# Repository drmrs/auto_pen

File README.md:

# Auto Penetrator

The project consists of a top to bottom open source 3d printed automatic penetrator.

If you can install and ssh into a linux box and have a 3d printed you should be able to make this.

# Gallery

[Youtube Video](https://www.youtube.com/watch?v=6sc3pjCMek8)

# Assembly & Use

Start with `hardware/README.md` file and follow the instructions from there.

# Open Source

The hardware is licenced under the CERN OHL (Basally GPL for hardware in so much as that can be enforced.)
The software is licenced under the Affero GPL.

# How To Help

Improvements are always welcome and PRs generally will be accepted.

Specific ways people can help include:
- Finding and fixing typos.
- Creating profiles for other raspberry pis beyond the original.
- Improving the code base.
- Adding more modes
- Improving the hardware diesign
    - Replacing glued on parts with screws
    - Add a screw mount for the USB adapter.
    - Adding a screw mount for the raspberry pi.

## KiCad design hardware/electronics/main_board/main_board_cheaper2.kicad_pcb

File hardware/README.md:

# Open Source Automatic Penetrator

## Building

Note in these images you may see some badly printed parts. You should aim to do better. These parts where the results of me wanting to finish and publish this documentation.

### Tools
1. Metric allen wrench set
2. 3D printer (300mmx300mm) is ideal but a smaller one works too.

### Materials

I will provide links to where I bought mine but you do not have to buy the same item or from the same source. My goals where to do this as economically as possible. Your goals may be different or the purchasing environment may have changed.  

The total cost of this build assuming you own all of the tools is: $201.98. This leaves you with many bolts, screws and parts that you can use for future projects.

If you already have some of these parts the price will be even lower.

#### Nuts & Bolts
1. x4 20mm (or longer) countersunk m3 screws [AliExpress $2.55](https://www.aliexpress.com/item/33007545714.html)
2. x16 m3 nuts [AliExpress $1.89](https://www.aliexpress.com/item/33031240097.html)
3. x4 10mm countersunk m3 screws [AliExpress $1.64](https://www.aliexpress.com/item/33007545714.html)
4. x2 12mm m3 screws [AliExpress $1.74](https://www.aliexpress.com/item/33007545714.html)

#### Electronics
1. NEMA34 Stepper Motor [Stepper Motor / Controller Kit AliExpress $84.19](https://www.aliexpress.com/item/33025486138.html)
2. Stepper Motor Controller [Part of Kit $0](#)
3. 24v 5A DC Power Supply [AliExpress $11.34](https://www.aliexpress.com/item/32905696401.html)
4. 24v USB charger [AliExpress $3.00](https://www.aliexpress.com/item/33031240097.html)
5. MicroUSB/USB C Cable (matching your raspberry pi) [Spare $0](#)
6. Raspberry Pi [Spare $40](https://www.raspberrypi.org/products/)
7. Barrel Jacks [Amazon $9.89](https://www.amazon.com/43x2pcs-Connectors-Security-Lighting-MILAPEAK)
8 18AWG Wire [AliExpress $4.88](https://www.aliexpress.com/item/32903241720.html)

#### Misc.
1. A roll of pla filament [Amazon $16](https://www.amazon.com/s?k=pla+1.75mm+filament)
2. Super Glue [Amazon $3.97](https://www.amazon.com/Loctite-Ultra-Control-4-Gram-1363589)
3. 14" Drawer Slide [Amazon $13.99](https://www.amazon.com/AmazonBasics-Bearing-Drawer-Slides-Plated-Steel/dp/B01MZC15UG)
4. Female Breadboard Jumper Wires [Amazon $6.90](https://www.amazon.com/gp/product/B01EV70C78)

### Step 1: Print Parts

#### 1.1. Main body

All items here printed at 0.3mm layer heights with 10% gyroid infill.

Load the `auto_pen/hardware/bin/main_body.amf` file into your slicer. Break it into its sub-components and lay them out as shown in the image below. If you need to print the items in separate prints this will be fine. If you need to split the items this is also fine. [I recommend you split the main case like this.](TODO)

If you want a pattern / ventilation (highly recommended) on the main case add a modifier block to the lid section (shown in green here) and set the infill to hex or some other cool pattern and set the top and bottom perimeters to 0. It should look like the below.

The two thin objects on thr right hand side of the image need extra strength and should be printed with 6 perimeters and 6 top and bottom layers.

#### 1.2 Rack & Pinion

All items here printed at 0.2mm layer heights with 10% gyroid infill with 4 perimeters and 5 top and bottom layers.

Load and print the rack and pinion from this file `auto_pen/hardware/bin/rack_and_pinion.amf`

It should look like this.

#### 1.3 Stepper Screw Adapters.

All items here printed at 0.2mm layer heights with 10% gyroid infill.

Load and print 4 copies of the screw adapter `auto_pen/hardware/bin/stepper_screw_adapters.amf`

The nut should be facing down and "from build plate only" supports should be enabled.

It should look like this.

Remove the supports and continue.

#### 1.4 Pusher Plate

There are two types of pusher plates, one uses rope to attach your "tool" to the plate, the other is designed for suction-cup tools. Choose the one you prefer.

All items here printed at 0.3mm layer heights with 15% gyroid infill and 8 perimeters.

Load and print the pusher plate you prefer `auto_pen/hardware/bin/rope_pusher_plate.amf` or `auto_pen/hardware/bin/suction_pusher_plate.amf`

The plate should be facing down.

It should look like this.

#### 1.5 Hinges

All items here printed at 0.2mm layer heights with 15% gyroid infill.

Load and print 2 copies of the hinge `auto_pen/hardware/bin/hinge.amf`

It should look like this.

You are Done Printing!

### Step 2: Electronics Assembly

Depending on exactly what you have your wiring may be dine is a slightly different way. If you purchased the exact same items as I did things should be very similar.

A few notes:
1. AC mains power is very dangerous. BE CAREFUL.
2. The Barrel Jack connected to 1 and 2 is connected to mains power. You need to decide the safest way to do this I used a GFIO plug but you may have a safer better way.
3. The Raspberry Pi is plugged into the stepper motor via female breadboard jumper wires with one side stripped off.
4. Different model Raspbery Pis have different GPIO / Ground pin layouts. [Refer to the appropriate documentation](https://www.raspberrypi.org/documentation/usage/gpio/) Make sure the GPIO PIN numbers match what is in the diagram.
5. The USB cable from the Pi should be plugged into the USB 24v adapter.
6. Non Raspberry Pi GPIO wiring is gone with the 18AWG wires.
7. I had to use a hammer to smash the clamps of the 24v USB adapter closed on the 18AWG wire.
8. Make sure your 24v 5A DC Power Supply is set to the correct mains voltage for your region (120v vs 240v)
9. For the default profile you will want to switch your motor controller to 1600steps/revolution. For me this was switch 6 only. Consult your stepper motor's documentation.

[For Full Size click here](https://raw.githubusercontent.com/drmrs/auto_pen/master/hardware/images/wires.png)

### Step 3: Electronics Testing

Assuming all your connections are sound connect mains power to the 24v 5A DC Power Supply. You may hear some sounds and some LEDs may turn on. If you can not turn the spindle of the stepper motor this is good news!

Precede to the `auto_pen/software/README.md` file to set up your Raspberry Pi.Once you can control your stepper motor precede to the next step.

### Step 4: Final Assembly

#### 4.1 Stepper motor

Press m3 nuts into the stepper motor adapter and press the who adapter into the stepper motor such that the the face is flush.

Note: Your nut should press substantially further in then in these images.

Place the case such that stepper motor face is out and the holes on the second face are down.

Slide the stepper motor into the case with the wire facing up.

Using 4 20mm or longer countersunk screws secure the stepper motor in place. These should be tight.

#### 4.2 Power Supply

The Mains -> 24vDC Power supply goes in the back with the connectors facing the stepper and the screw holes facing down.

Push 10mm countersunk screws through the bottom and line them up with with the screw holes.

With one finger press a nut down onto the screw and use an allen wrench to tighten from the outside.

Now is a good time to run the USB cable. RUn it from the USB adapter to the right hand side of the box above the power supply.

#### 4.3 Stepper Motor Controller

Mount the controller in the same way you mounted the power supply positioning the raspberry pi to the right and the USB power adapter above the stepper motor to the left.

The pi might be a tight angle but it should fit. I recommend positioning the PI so the SD card is readily available.

When you are done it should look like this:

Keep the mains power supply above the stepper motor for now.

You may want to retest things before you continue.

#### 4.4 Drawer Slide and Pusher.

Attach the slide to the "feet" via 2 10mm m3 screws. Tighten and ensure they are perpendicular to the slide.

Apply a generous amount of super glue to the top of the feet and place the main case on it such that:

1. The side of the rail is flush against the case.
2. The back of the rail is flush with the back of the case (raspberry pi side)
3. The extending bar is near the stepper motor.

Let dry for 1 hour.

Using 2 12mm m3 screws and nuts lock the rope based pusher into place.

#### 4.5 Rack & Pinion

 Press the gear onto the stepper motor.
 
 With the slider in the locked position position the rack that the gear is not engaged with it. This should be by a few mm. See the photo below. We give it this extra space so in case something goes wrong the rack isn't slammed into the lock.
 
 Glue it in position.

 #### Cover, Hinges and Power
 
 After printing the hinges may be VERY stiff. move them til they loosen up.
 
 With the hinges in the 90 degree position glue them flush against the upper two corners. THe side with the hole is the top. The hole should be on the left-ish side. (See photo below.)
 
 Allow to dry for 30 min.
 
 With the hinges in the 90 angle glue them against the case such that the lid is flush against the case. Be sure not to glue the hinge to the top of the lid.
 
  Allow to dry for 30 min.

 The mains power inlet should friction fit into the hole. Glue it in.

 Close and you are done!

 If the lid is a bit loose you could use some tape or a small drop of super glue to hold it in place.
 
 Enjoy.

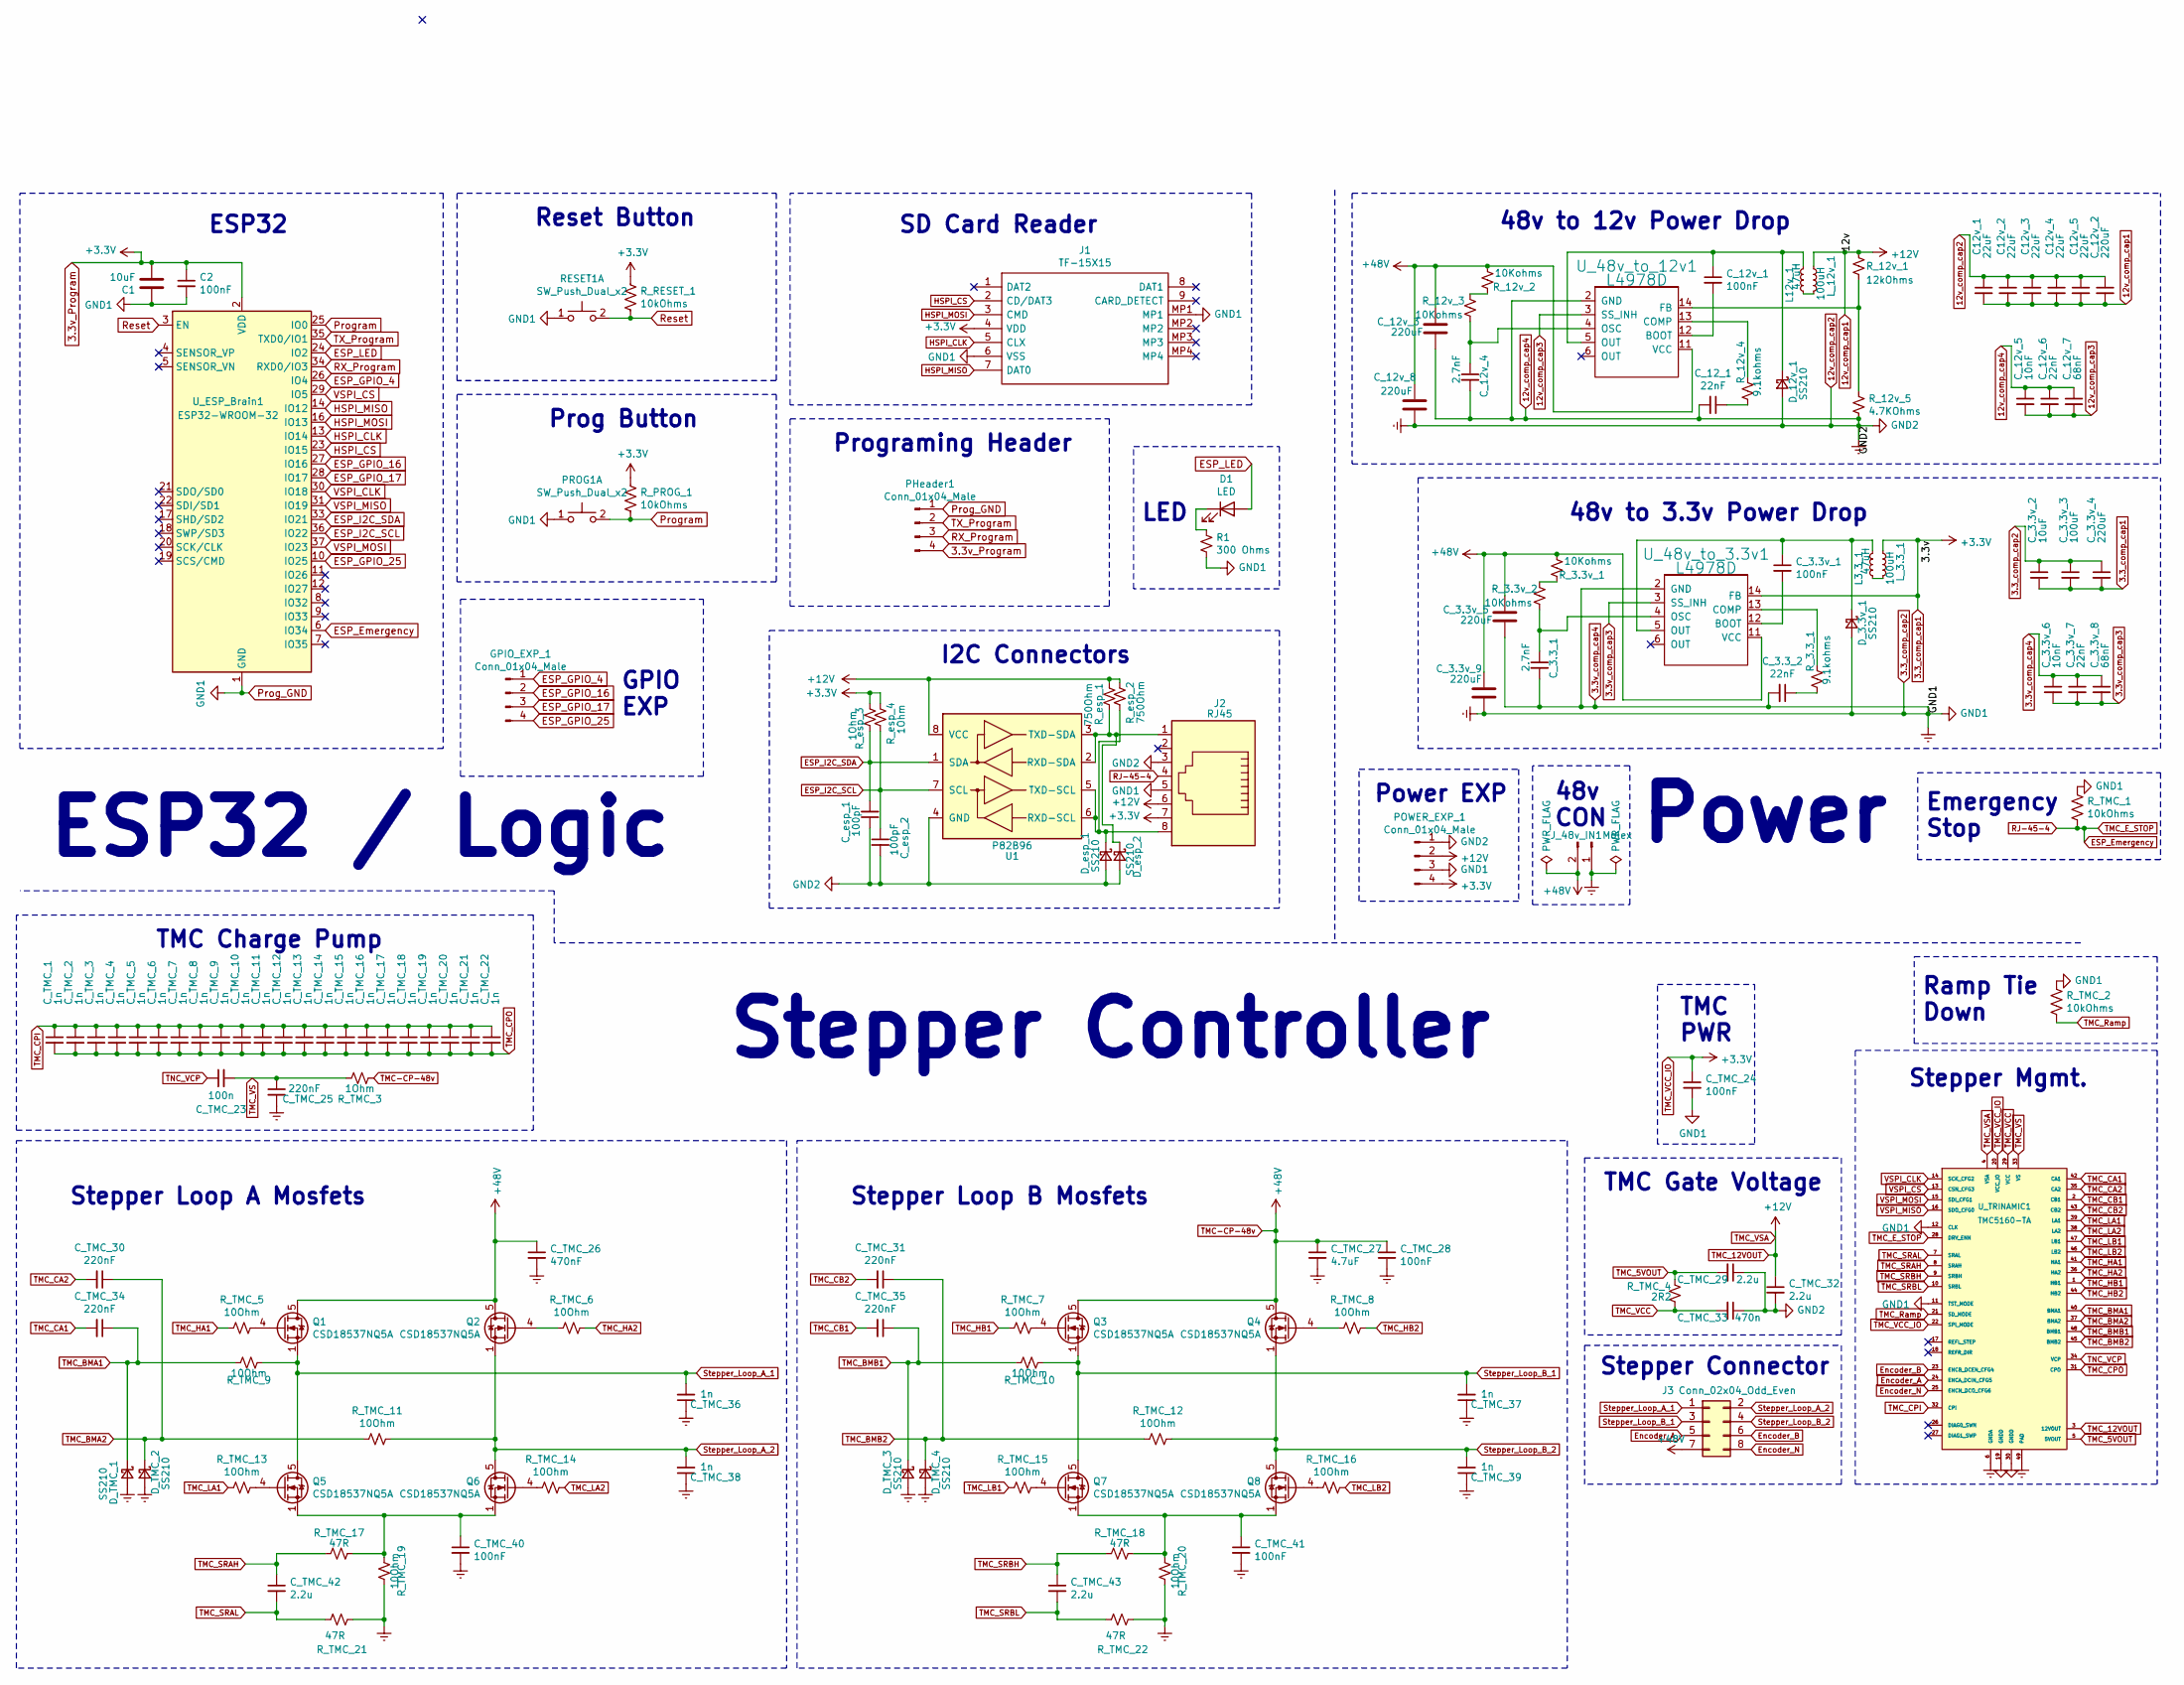
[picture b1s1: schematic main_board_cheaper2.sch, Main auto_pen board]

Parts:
C1: 10uF; C_0402_1005Metric; JLCPCB C15525
C2: 100nF; C_0402_1005Metric; JLCPCB C1525
C12v_1, C12v_2, C12v_3, C12v_4, C12v_5: 22uF; C_0805_2012Metric; JLCPCB C45783
C_3.3_1, C_12v_4: 2.7nF; C_0603_1608Metric; JLCPCB C1609
C_3.3_2, C_3.3v_7, C_12_1, C_12v_6: 22nF; C_0805_2012Metric; JLCPCB C1729
C_3.3v_1, C_12v_1: 100nF; C_0402_1005Metric; JLCPCB C1525
C_3.3v_2: 10uF; C_0402_1005Metric; JLCPCB C15525
C_3.3v_3: 100uF; CP_EIA-3528-15_AVX-H; JLCPCB C16133
C_3.3v_4, C_3.3v_5, C_3.3v_9, C_12v_2, C_12v_3, C_12v_8: 220uF; C_Elec_10x10.2; JLCPCB C3358
C_3.3v_6, C_12v_5: 10nF; C_0805_2012Metric; JLCPCB C1710
C_3.3v_8, C_12v_7: 68nF; C_0603_1608Metric; JLCPCB C31658
C_TMC_1, C_TMC_2, C_TMC_3, C_TMC_4, C_TMC_5, C_TMC_6, C_TMC_7, C_TMC_8, C_TMC_9, C_TMC_10, C_TMC_11, C_TMC_12, C_TMC_13, C_TMC_14, C_TMC_15, C_TMC_16, C_TMC_17, C_TMC_18, C_TMC_19, C_TMC_20, C_TMC_21, C_TMC_22, C_TMC_36, C_TMC_37, C_TMC_38, C_TMC_39: 1n; C_1206_3216Metric; JLCPCB C35216
C_TMC_23: 100n; C_0402_1005Metric; JLCPCB C1525
C_TMC_24: 100nF; C_0402_1005Metric; JLCPCB C1525
C_TMC_25: 220nF; C_0805_2012Metric; JLCPCB C5378
C_TMC_26: 470nF; C_0805_2012Metric; JLCPCB C13967
C_TMC_27: 4.7uF; C_1206_3216Metric; JLCPCB C29823
C_TMC_28, C_TMC_40, C_TMC_41: 100nF; C_1206_3216Metric; JLCPCB C24497
C_TMC_29, C_TMC_32: 2.2u; C_0603_1608Metric; JLCPCB C23630
C_TMC_30, C_TMC_31, C_TMC_34, C_TMC_35: 220nF; C_1206_3216Metric; JLCPCB C1857
C_TMC_33: 470n; C_0603_1608Metric; JLCPCB C1623
C_TMC_42, C_TMC_43: 2.2u; C_1206_3216Metric; JLCPCB C50254
C_esp_1, C_esp_2: 100pF; C_0603_1608Metric; JLCPCB C14858
D1: LED; LED_0603_1608Metric; JLCPCB C72041
D_3.3v_1, D_12v_1: SS210; D_SMA; JLCPCB C14996
D_TMC_1, D_TMC_2, D_TMC_3, D_TMC_4: SS210; D_SMA; JLCPCB C14996
D_esp_1, D_esp_2: SS210; D_SMA; JLCPCB C14996
GPIO_EXP_1: Conn_01x04_Male; PinHeader_1x04_P2.54mm_Vertical; JLCPCB C124378
J1: TF-15X15; TF15X15; Manufacturer_Part_Number TF-15X15; JLCPCB C111196
J2: RJ45; 5555166-1; JLCPCB C305991
J3: Conn_02x04_Odd_Even; Molex_Micro-Fit_3.0_43045-0812_2x04_P3.00mm_Vertical; JLCPCB C277661
J_48v_IN1: Molex; Molex_Micro-Fit_3.0_43045-0212_2x01_P3.00mm_Vertical; JLCPCB C293362
L3.3_1, L12v_1: 47uH; L_0805_2012Metric; JLCPCB C14304
L_3.3_1, L_12v_1: 100uH; L_0805_2012Metric; JLCPCB C68035
PHeader1: Conn_01x04_Male; PinHeader_1x04_P2.54mm_Vertical; JLCPCB C124378
POWER_EXP_1: Conn_01x04_Male; PinHeader_1x04_P2.54mm_Vertical; JLCPCB C124378
PROG1: SW_Push_Dual_x2; SW_Push_1P1T_NO_6x6mm_H9.5mm; JLCPCB C381038
Q1, Q2, Q3, Q4, Q5, Q6, Q7, Q8: CSD18537NQ5A; TDSON-8-1; JLCPCB C72266
R1: 300 Ohms; R_0805_2012Metric; JLCPCB C17617
RESET1: SW_Push_Dual_x2; SW_Push_1P1T_NO_6x6mm_H9.5mm; JLCPCB C381038
R_3.3_1, R_12v_4: 9.1kohms; R_0805_2012Metric; JLCPCB C17855
R_3.3v_1, R_3.3v_2, R_12v_2, R_12v_3: 10Kohms; R_1206_3216Metric; JLCPCB C17902
R_12v_1: 12kOhms; R_0805_2012Metric; JLCPCB C17444
R_12v_5: 4.7KOhms; R_1206_3216Metric; JLCPCB C17936
R_PROG_1: 10kOhms; R_1206_3216Metric; JLCPCB C17902
R_RESET_1: 10kOhms; R_1206_3216Metric; JLCPCB C17902
R_TMC_1, R_TMC_2: 10kOhms; R_1206_3216Metric; JLCPCB C17902
R_TMC_3: 1Ohm; R_1206_3216Metric; JLCPCB C17928
R_TMC_4: 2R2; R_0805_2012Metric; JLCPCB C17521
R_TMC_5, R_TMC_6, R_TMC_7, R_TMC_8, R_TMC_9, R_TMC_10, R_TMC_11, R_TMC_12, R_TMC_13, R_TMC_14, R_TMC_15, R_TMC_16, R_TMC_19, R_TMC_20: 10Ohm; R_1206_3216Metric; JLCPCB C17903
R_TMC_17, R_TMC_18, R_TMC_21, R_TMC_22: 47R; R_0805_2012Metric; JLCPCB C17714
R_esp_1, R_esp_2: 750Ohm; R_1206_3216Metric; JLCPCB C17985
R_esp_3, R_esp_4: 1Ohm; R_1206_3216Metric; JLCPCB C17928
U1: P82B96; SO-8_3.9x4.9mm_P1.27mm; JLCPCB C32103
U_48v_to_3.3v1, U_48v_to_12v1: L4978D; SOIC-16W_7.5x10.3mm_P1.27mm; JLCPCB C93521
U_ESP_Brain1: ESP32-WROOM-32; JLCPCB C82899
U_TRINAMIC1: TMC5160-TA; eTQFP48; MPN TMC5160-TA; Digi-Key_PN 1460-1249-ND

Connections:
3.3_comp_cap1: C1.2, C2.1, C_3.3v_2.2, C_3.3v_3.2, C_3.3v_4.2, C_TMC_24.1, J1.4 (VDD), J2.7, L_3.3_1.1, PHeader1.4, POWER_EXP_1.4, R_PROG_1.1, R_RESET_1.1, R_esp_3.2, R_esp_4.1, U_48v_to_3.3v1.14 (FB), U_ESP_Brain1.2 (VDD), U_TRINAMIC1.20 (VCC_IO), U_TRINAMIC1.22 (SPI_MODE)
3.3v_comp_cap3: C_3.3v_6.2, C_3.3v_7.2, C_3.3v_8.2, U_48v_to_3.3v1.3 (SS_INH)
12v_comp_cap1: C12v_1.2, C12v_2.2, C12v_3.2, C12v_4.2, C12v_5.2, C_12v_2.2, C_TMC_32.1, J2.6, L_12v_1.1, POWER_EXP_1.2, R_12v_1.1, R_esp_1.2, R_esp_2.1, U1.8 (VCC), U_TRINAMIC1.3 (12VOUT), U_TRINAMIC1.4 (VSA)
12v_comp_cap2: C1.1, C2.2, C12v_1.1, C12v_2.1, C12v_3.1, C12v_4.1, C12v_5.1, C_3.3_1.2, C_3.3_2.2, C_3.3v_2.1, C_3.3v_3.1, C_3.3v_4.1, C_3.3v_5.2, C_3.3v_6.1, C_3.3v_7.1, C_3.3v_8.1, C_3.3v_9.2, C_12_1.2, C_12v_2.1, C_12v_3.2, C_12v_4.2, C_12v_5.1, C_12v_6.1, C_12v_7.1, C_12v_8.2, C_TMC_24.2, C_TMC_25.2, C_TMC_26.2, C_TMC_27.2, C_TMC_28.2, C_TMC_29.1, C_TMC_32.2, C_TMC_33.1, C_TMC_36.1, C_TMC_37.1, C_TMC_38.1, C_TMC_39.1, C_TMC_40.2, C_TMC_41.2, C_esp_1.1, C_esp_2.2, D_3.3v_1.2 (A), D_12v_1.2 (A), D_TMC_1.2 (A), D_TMC_2.2 (A), D_TMC_3.2 (A), D_TMC_4.2 (A), D_esp_1.2 (A), D_esp_2.2 (A), J1.6 (VSS), J1.MP1, J2.3, J2.5, J_48v_IN1.1, PHeader1.1, POWER_EXP_1.1, POWER_EXP_1.3, PROG1.1 (C), R1.1, RESET1.1 (C), R_12v_5.2, R_TMC_1.1, R_TMC_2.1, R_TMC_19.2, R_TMC_20.2, R_TMC_21.2, R_TMC_22.2, U1.4 (GND), U_48v_to_3.3v1.2 (GND), U_48v_to_12v1.2 (GND), U_ESP_Brain1.1 (GND), U_ESP_Brain1.15 (GND), U_ESP_Brain1.38 (GND), U_ESP_Brain1.39 (GND), U_TRINAMIC1.6 (GNDA), U_TRINAMIC1.11 (TST_MODE), U_TRINAMIC1.12 (CLK), U_TRINAMIC1.19 (GNDD), U_TRINAMIC1.30 (GNDD), U_TRINAMIC1.49 (PAD)
12v_comp_cap3: C_12v_5.2, C_12v_6.2, C_12v_7.2, U_48v_to_12v1.3 (SS_INH)
ESP_Emergency: J2.4, R_TMC_1.2, U_ESP_Brain1.6 (IO34), U_TRINAMIC1.28 (DRV_ENN)
ESP_GPIO_4: GPIO_EXP_1.1, U_ESP_Brain1.26 (IO4)
ESP_GPIO_16: GPIO_EXP_1.2, U_ESP_Brain1.27 (IO16)
ESP_GPIO_17: GPIO_EXP_1.3, U_ESP_Brain1.28 (IO17)
ESP_GPIO_25: GPIO_EXP_1.4, U_ESP_Brain1.10 (IO25)
ESP_I2C_SCL: C_esp_2.1, R_esp_4.2, U1.7 (SCL), U_ESP_Brain1.36 (IO22)
ESP_I2C_SDA: C_esp_1.2, R_esp_3.1, U1.1 (SDA), U_ESP_Brain1.33 (IO21)
ESP_LED: D1.2 (A), U_ESP_Brain1.24 (IO2)
Encoder_A: J3.5, U_TRINAMIC1.24 (ENCA_DCIN_CFG5)
Encoder_B: J3.6, U_TRINAMIC1.23 (ENCB_DCEN_CFG4)
Encoder_N: J3.8, U_TRINAMIC1.25 (ENCN_DCO_CFG6)
HSPI_CLK: J1.5 (CLX), U_ESP_Brain1.13 (IO14)
HSPI_CS: J1.2 (CD/DAT3), U_ESP_Brain1.23 (IO15)
HSPI_MISO: J1.7 (DAT0), U_ESP_Brain1.14 (IO12)
HSPI_MOSI: J1.3 (CMD), U_ESP_Brain1.16 (IO13)
unnamed: C_3.3_1.1, R_3.3v_2.2, U_48v_to_3.3v1.4 (OSC)
unnamed: C_3.3_2.1, R_3.3_1.2
unnamed: C_3.3v_1.1, D_3.3v_1.1 (K), L3.3_1.2, U_48v_to_3.3v1.5 (OUT)
unnamed: C_3.3v_1.2, U_48v_to_3.3v1.12 (BOOT)
unnamed: C_12_1.1, R_12v_4.2
unnamed: C_12v_1.1, D_12v_1.1 (K), L12v_1.2, U_48v_to_12v1.5 (OUT)
unnamed: C_12v_1.2, U_48v_to_12v1.12 (BOOT)
unnamed: C_12v_4.1, R_12v_3.2, U_48v_to_12v1.4 (OSC)
unnamed: C_TMC_40.1, Q5.1 (S), Q5.2 (S), Q5.3 (S), Q6.1 (S), Q6.2 (S), Q6.3 (S), R_TMC_17.2, R_TMC_19.1
unnamed: C_TMC_41.1, Q7.1 (S), Q7.2 (S), Q7.3 (S), Q8.1 (S), Q8.2 (S), Q8.3 (S), R_TMC_18.2, R_TMC_20.1
unnamed: D1.1 (K), R1.2
unnamed: D_esp_1.1 (K), J2.8, R_esp_2.2, U1.5 (TXD-SCL), U1.6 (RXD-SCL)
unnamed: D_esp_2.1 (K), J2.1, R_esp_1.1, U1.2 (RXD-SDA), U1.3 (TXD-SDA)
unnamed: L3.3_1.1, L_3.3_1.2
unnamed: L12v_1.1, L_12v_1.2
unnamed: Q1.4 (G), R_TMC_5.1
unnamed: Q2.4 (G), R_TMC_6.2
unnamed: Q3.4 (G), R_TMC_7.1
unnamed: Q4.4 (G), R_TMC_8.2
unnamed: Q5.4 (G), R_TMC_13.1
unnamed: Q6.4 (G), R_TMC_14.2
unnamed: Q7.4 (G), R_TMC_15.1
unnamed: Q8.4 (G), R_TMC_16.2
unnamed: R_3.3_1.1, U_48v_to_3.3v1.13 (COMP)
unnamed: R_3.3v_1.1, R_3.3v_2.1
unnamed: R_12v_1.2, R_12v_5.1, U_48v_to_12v1.14 (FB)
unnamed: R_12v_2.1, R_12v_3.1
unnamed: R_12v_4.1, U_48v_to_12v1.13 (COMP)
Program: PROG1.2 (D), R_PROG_1.2, U_ESP_Brain1.25 (IO0)
RX_Program: PHeader1.3, U_ESP_Brain1.34 (RXD0/IO3)
Reset: RESET1.2 (D), R_RESET_1.2, U_ESP_Brain1.3 (EN)
Stepper_Loop_A_1: C_TMC_36.2, J3.1, Q1.1 (S), Q1.2 (S), Q1.3 (S), Q5.5 (D), R_TMC_9.1
Stepper_Loop_A_2: C_TMC_38.2, J3.2, Q2.1 (S), Q2.2 (S), Q2.3 (S), Q6.5 (D), R_TMC_11.1
Stepper_Loop_B_1: C_TMC_37.2, J3.3, Q3.1 (S), Q3.2 (S), Q3.3 (S), Q7.5 (D), R_TMC_10.1
Stepper_Loop_B_2: C_TMC_39.2, J3.4, Q4.1 (S), Q4.2 (S), Q4.3 (S), Q8.5 (D), R_TMC_12.1
TMC-CP-48v: C_3.3v_5.1, C_3.3v_9.1, C_12v_3.1, C_12v_8.1, C_TMC_26.1, C_TMC_27.1, C_TMC_28.1, J3.7, J_48v_IN1.2, Q1.5 (D), Q2.5 (D), Q3.5 (D), Q4.5 (D), R_3.3v_1.2, R_12v_2.2, R_TMC_3.2, U_48v_to_3.3v1.11 (VCC), U_48v_to_12v1.11 (VCC)
TMC_5VOUT: C_TMC_29.2, R_TMC_4.1, U_TRINAMIC1.5 (5VOUT)
TMC_BMA1: C_TMC_34.1, D_TMC_1.1 (K), R_TMC_9.2, U_TRINAMIC1.40 (BMA1)
TMC_BMA2: C_TMC_30.1, D_TMC_2.1 (K), R_TMC_11.2, U_TRINAMIC1.37 (BMA2)
TMC_BMB1: C_TMC_35.1, D_TMC_3.1 (K), R_TMC_10.2, U_TRINAMIC1.48 (BMB1)
TMC_BMB2: C_TMC_31.1, D_TMC_4.1 (K), R_TMC_12.2, U_TRINAMIC1.45 (BMB2)
TMC_CA1: C_TMC_34.2, U_TRINAMIC1.42 (CA1)
TMC_CA2: C_TMC_30.2, U_TRINAMIC1.35 (CA2)
TMC_CB1: C_TMC_35.2, U_TRINAMIC1.2 (CB1)
TMC_CB2: C_TMC_31.2, U_TRINAMIC1.43 (CB2)
TMC_CPI: C_TMC_1.1, C_TMC_2.1, C_TMC_3.1, C_TMC_4.1, C_TMC_5.1, C_TMC_6.1, C_TMC_7.1, C_TMC_8.1, C_TMC_9.1, C_TMC_10.1, C_TMC_11.1, C_TMC_12.1, C_TMC_13.1, C_TMC_14.1, C_TMC_15.1, C_TMC_16.1, C_TMC_17.1, C_TMC_18.1, C_TMC_19.1, C_TMC_20.1, C_TMC_21.1, C_TMC_22.1, U_TRINAMIC1.32 (CPI)
TMC_CPO: C_TMC_1.2, C_TMC_2.2, C_TMC_3.2, C_TMC_4.2, C_TMC_5.2, C_TMC_6.2, C_TMC_7.2, C_TMC_8.2, C_TMC_9.2, C_TMC_10.2, C_TMC_11.2, C_TMC_12.2, C_TMC_13.2, C_TMC_14.2, C_TMC_15.2, C_TMC_16.2, C_TMC_17.2, C_TMC_18.2, C_TMC_19.2, C_TMC_20.2, C_TMC_21.2, C_TMC_22.2, U_TRINAMIC1.31 (CPO)
TMC_HA1: R_TMC_5.2, U_TRINAMIC1.41 (HA1)
TMC_HA2: R_TMC_6.1, U_TRINAMIC1.36 (HA2)
TMC_HB1: R_TMC_7.2, U_TRINAMIC1.1 (HB1)
TMC_HB2: R_TMC_8.1, U_TRINAMIC1.44 (HB2)
TMC_LA1: R_TMC_13.2, U_TRINAMIC1.39 (LA1)
TMC_LA2: R_TMC_14.1, U_TRINAMIC1.38 (LA2)
TMC_LB1: R_TMC_15.2, U_TRINAMIC1.47 (LB1)
TMC_LB2: R_TMC_16.1, U_TRINAMIC1.46 (LB2)
TMC_Ramp: R_TMC_2.2, U_TRINAMIC1.21 (SD_MODE)
TMC_SRAH: C_TMC_42.1, R_TMC_17.1, U_TRINAMIC1.8 (SRAH)
TMC_SRAL: C_TMC_42.2, R_TMC_21.1, U_TRINAMIC1.7 (SRAL)
TMC_SRBH: C_TMC_43.1, R_TMC_18.1, U_TRINAMIC1.9 (SRBH)
TMC_SRBL: C_TMC_43.2, R_TMC_22.1, U_TRINAMIC1.10 (SRBL)
TMC_VCC: C_TMC_33.2, R_TMC_4.2, U_TRINAMIC1.29 (VCC)
TMC_VS: C_TMC_23.2, C_TMC_25.1, R_TMC_3.1, U_TRINAMIC1.33 (VS)
TNC_VCP: C_TMC_23.1, U_TRINAMIC1.34 (VCP)
TX_Program: PHeader1.2, U_ESP_Brain1.35 (TXD0/IO1)
VSPI_CLK: U_ESP_Brain1.30 (IO18), U_TRINAMIC1.14 (SCK_CFG2)
VSPI_CS: U_ESP_Brain1.29 (IO5), U_TRINAMIC1.13 (CSN_CFG3)
VSPI_MISO: U_ESP_Brain1.31 (IO19), U_TRINAMIC1.16 (SDO_CFG0)
VSPI_MOSI: U_ESP_Brain1.37 (IO23), U_TRINAMIC1.15 (SDI_CFG1)

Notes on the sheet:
Programing Header
ESP32
48v to 12v Power Drop
48v to 3.3v Power Drop
48v CON
Prog Button
Reset Button
TMC Gate Voltage
TMC PWR
TMC Charge Pump
Stepper Loop A Mosfets
Stepper Loop B Mosfets
Stepper Connector
Stepper Mgmt.
SD Card Reader
Power
ESP32 / Logic
I2C Connectors
Emergency Stop
GPIO EXP
LED
Ramp Tie Down
Stepper Controller
Power EXP

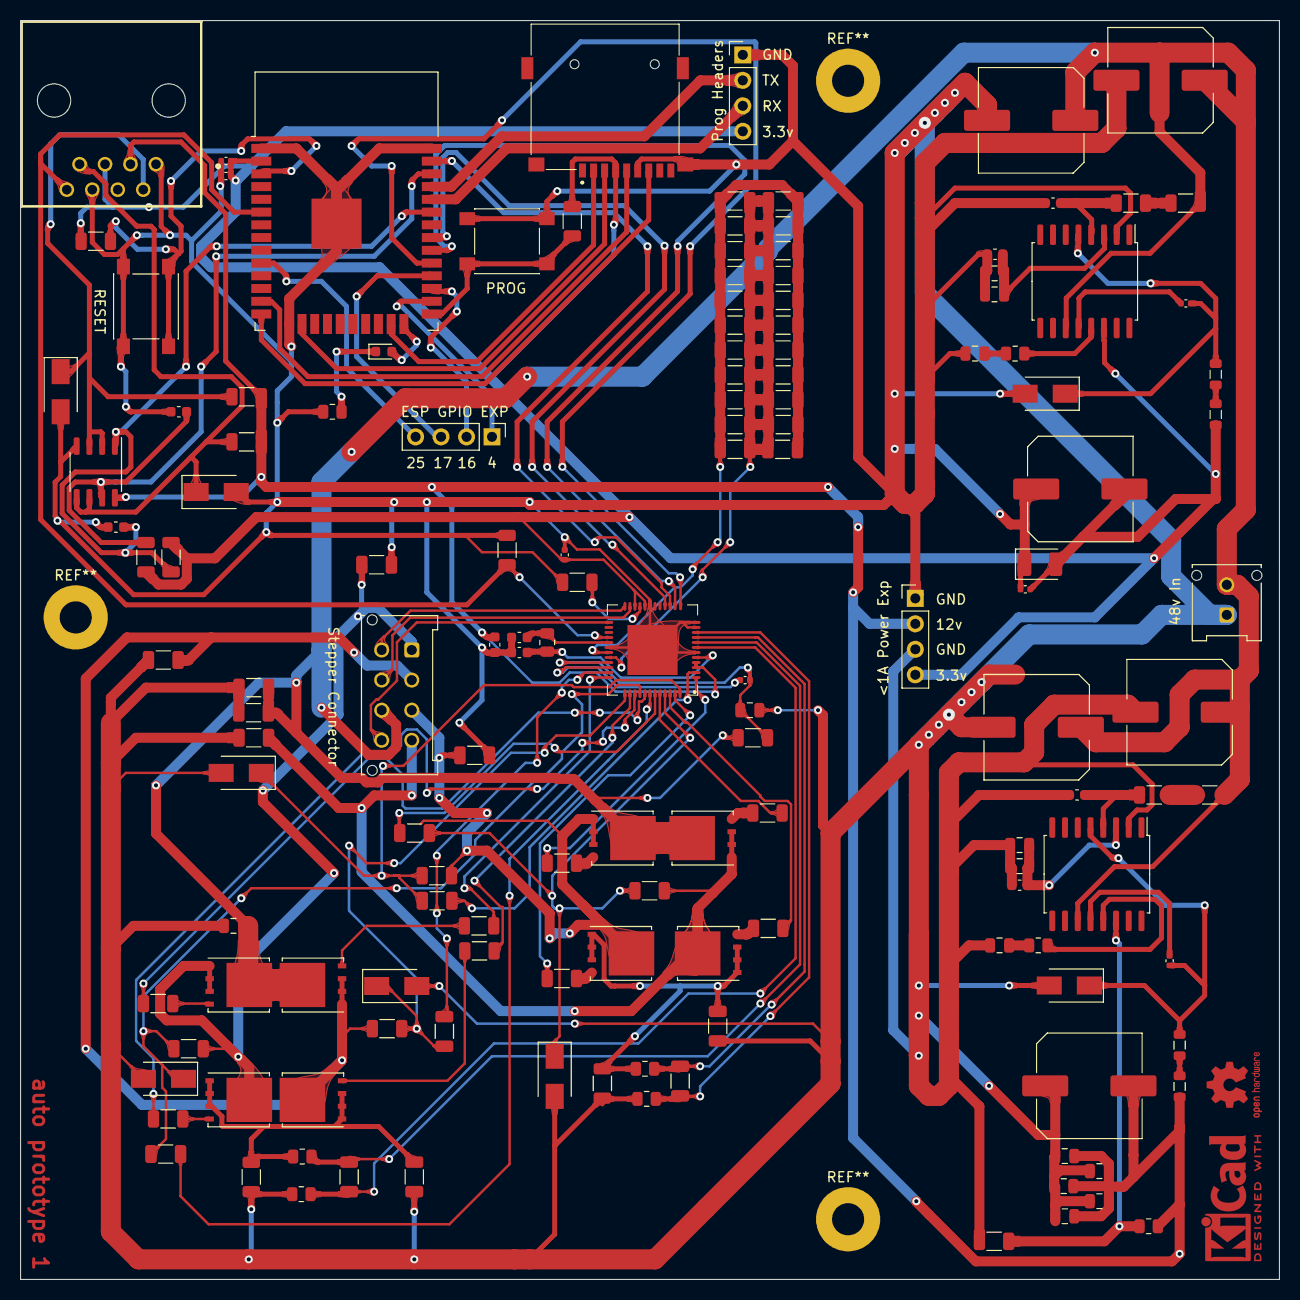
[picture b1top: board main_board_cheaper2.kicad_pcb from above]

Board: 2 copper layers, 125.5 x 125.5 mm, 144 parts (0 on the bottom side), 88 nets.

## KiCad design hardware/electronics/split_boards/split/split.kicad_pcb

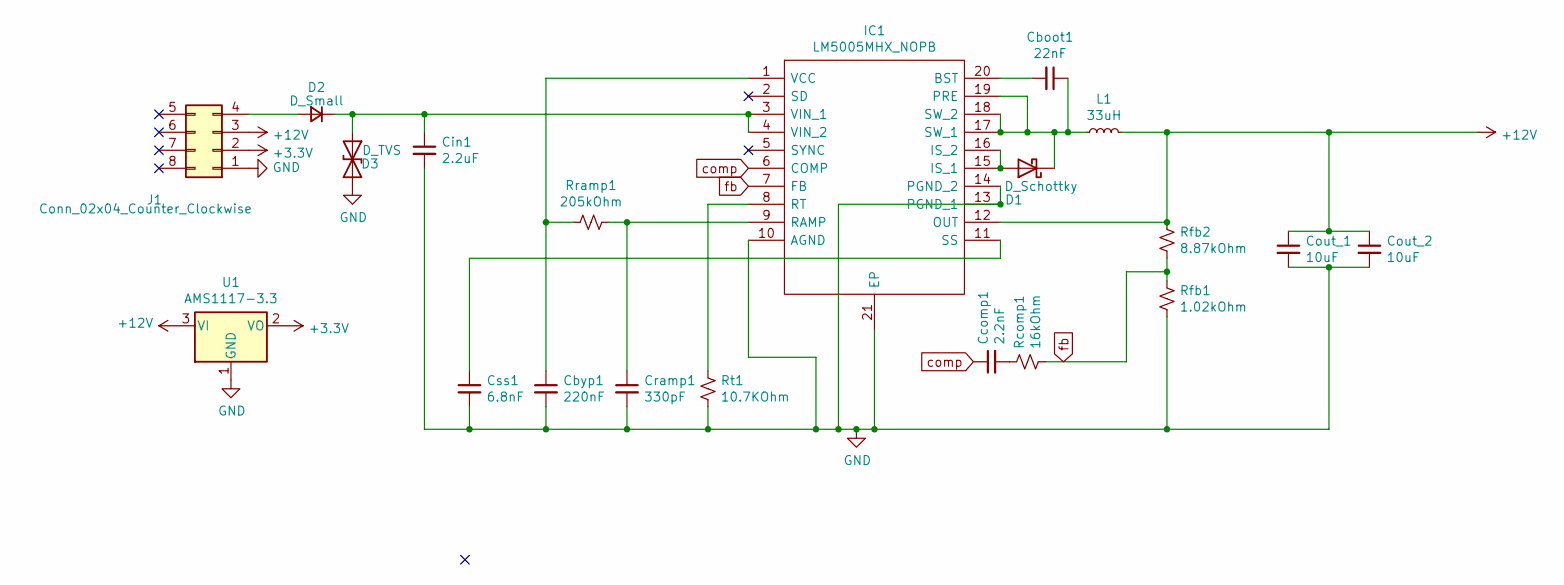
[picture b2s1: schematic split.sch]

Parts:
Cboot1: 22nF; C_0805_2012Metric; JLCPCB C1729
Cbyp1: 220nF; C_0402_1005Metric; JLCPCB C16772
Ccomp1: 2.2nF; C_0805_2012Metric; JLCPCB C28260
Cin1: 2.2uF; C_1210_3225Metric; JLCPCB C153036
Cout_1, Cout_2: 10uF; C_1206_3216Metric; JLCPCB C13585
Cramp1: 330pF; C_0603_1608Metric; JLCPCB C1664
Css1: 6.8nF; C_0603_1608Metric; JLCPCB C1631
D1: D_Schottky; D_SMB; JLCPCB C110479
D2: D_Small; D_SMC; JLCPCB C143035
D3: D_TVS; D_SMC; JLCPCB C133645
IC1: LM5005MHX_NOPB; SOP65P640X110-21N; Manufacturer_Part_Number LM5005MHX/NOPB; Mouser Part Number 926-LM5005MHX/NOPB
J1: Conn_02x04_Counter_Clockwise; PINREX_733-72-08TB10; JLCPCB C402783
L1: 33uH; SWPA8040S330MT; JLCPCB C83467
Rcomp1: 16kOhm; R_0805_2012Metric; JLCPCB C17490
Rfb1: 1.02kOhm; R_0805_2012Metric; JLCPCB C17369
Rfb2: 8.87kOhm; R_0805_2012Metric; JLCPCB C37551
Rramp1: 205kOhm; R_0805_2012Metric; JLCPCB C17541
Rt1: 10.7KOhm; R_0603_1608Metric; JLCPCB C22857
U1: AMS1117-3.3; SOT-223-3_TabPin2; JLCPCB C6186

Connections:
+3V3: J1.2, U1.2 (VO)
+12V: Cout_1.1, Cout_2.1, IC1.12 (OUT), J1.3, L1.2, Rfb2.1, U1.3 (VI)
GND: Cbyp1.2, Cin1.2, Cout_1.2, Cout_2.2, Cramp1.2, Css1.2, D3.2 (A2), IC1.10 (AGND), IC1.13 (PGND_1), IC1.14 (PGND_2), IC1.21 (EP), J1.1, Rfb1.2, Rt1.2, U1.1 (GND)
unnamed: Cboot1.1, D1.1 (K), IC1.17 (SW_1), IC1.18 (SW_2), IC1.19 (PRE), L1.1
unnamed: Cboot1.2, IC1.20 (BST)
unnamed: Cbyp1.1, IC1.1 (VCC), Rramp1.1
unnamed: Ccomp1.2, Rcomp1.1
unnamed: Cin1.1, D2.1 (K), D3.1 (A1), IC1.3 (VIN_1), IC1.4 (VIN_2)
unnamed: Cramp1.1, IC1.9 (RAMP), Rramp1.2
unnamed: Css1.1, IC1.11 (SS)
unnamed: D1.2 (A), IC1.15 (IS_1), IC1.16 (IS_2)
unnamed: D2.2 (A), J1.4
unnamed: IC1.8 (RT), Rt1.1
comp: Ccomp1.1, IC1.6 (COMP)
fb: IC1.7 (FB), Rcomp1.2, Rfb1.1, Rfb2.2

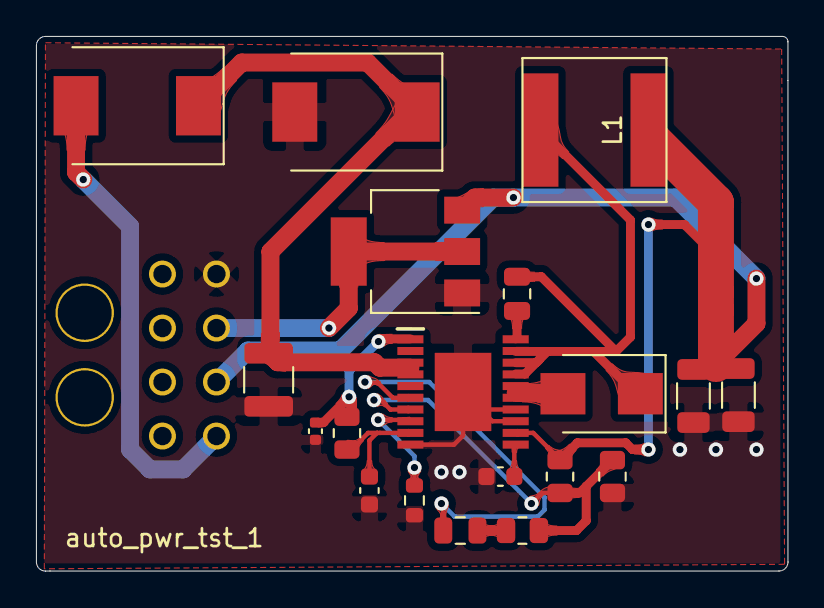
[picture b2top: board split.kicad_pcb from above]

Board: 2 copper layers, 41.8 x 29.7 mm, 20 parts (0 on the bottom side), 15 nets.
